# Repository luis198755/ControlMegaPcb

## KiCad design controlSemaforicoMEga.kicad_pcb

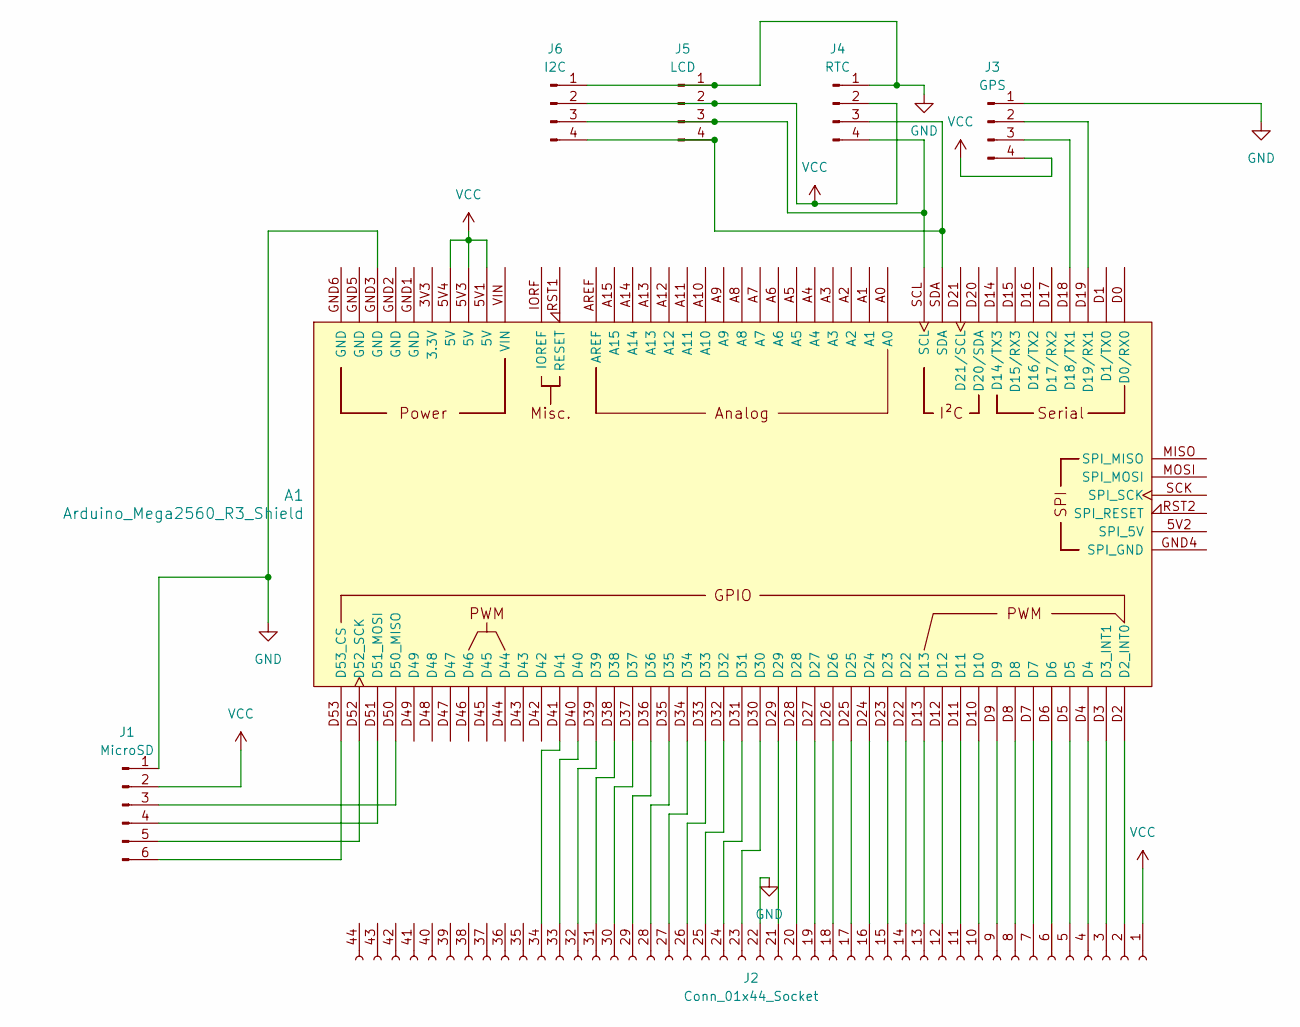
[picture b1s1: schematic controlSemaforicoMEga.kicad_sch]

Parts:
A1: Arduino_Mega2560_R3_Shield
J1: MicroSD; PinHeader_1x06_P2.54mm_Vertical
J2: Conn_01x44_Socket; con22sem
J3: GPS; PinHeader_1x04_P2.54mm_Vertical
J4: RTC; PinHeader_1x04_P2.54mm_Vertical
J5: LCD; PinHeader_1x04_P2.54mm_Vertical
J6: I2C; PinHeader_1x04_P2.54mm_Vertical

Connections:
GND: A1.GND3 (GND), J1.1, J2.22, J3.1, J4.1, J5.1, J6.1
unnamed: A1.D2 (D2_INT0), J2.2
unnamed: A1.D3 (D3_INT1), J2.3
unnamed: A1.D18 (D18/TX1), J3.3
unnamed: A1.D19 (D19/RX1), J3.2
unnamed: A1.D50 (D50_MISO), J1.3
unnamed: A1.D51 (D51_MOSI), J1.4
unnamed: A1.D52 (D52_SCK), J1.5
unnamed: A1.D53 (D53_CS), J1.6
unnamed: A1.D4, J2.4
unnamed: A1.D5, J2.5
unnamed: A1.D6, J2.6
unnamed: A1.D7, J2.7
unnamed: A1.D8, J2.8
unnamed: A1.D9, J2.9
unnamed: A1.D10, J2.10
unnamed: A1.D11, J2.11
unnamed: A1.D12, J2.12
unnamed: A1.D13, J2.13
unnamed: A1.D22, J2.14
unnamed: A1.D23, J2.15
unnamed: A1.D24, J2.16
unnamed: A1.D25, J2.17
unnamed: A1.D26, J2.18
unnamed: A1.D27, J2.19
unnamed: A1.D28, J2.20
unnamed: A1.D29, J2.21
unnamed: A1.D30, J2.23
unnamed: A1.D31, J2.24
unnamed: A1.D32, J2.25
unnamed: A1.D33, J2.26
unnamed: A1.D34, J2.27
unnamed: A1.D35, J2.28
unnamed: A1.D36, J2.29
unnamed: A1.D37, J2.30
unnamed: A1.D38, J2.31
unnamed: A1.D39, J2.32
unnamed: A1.D40, J2.33
unnamed: A1.D41, J2.34
unnamed: A1.SDA, J4.3, J5.4, J6.4
unnamed: A1.SCL, J4.4, J5.3, J6.3
VCC: A1.5V1 (5V), A1.5V3 (5V), A1.5V4 (5V), J1.2, J2.1, J3.4, J4.2, J5.2, J6.2

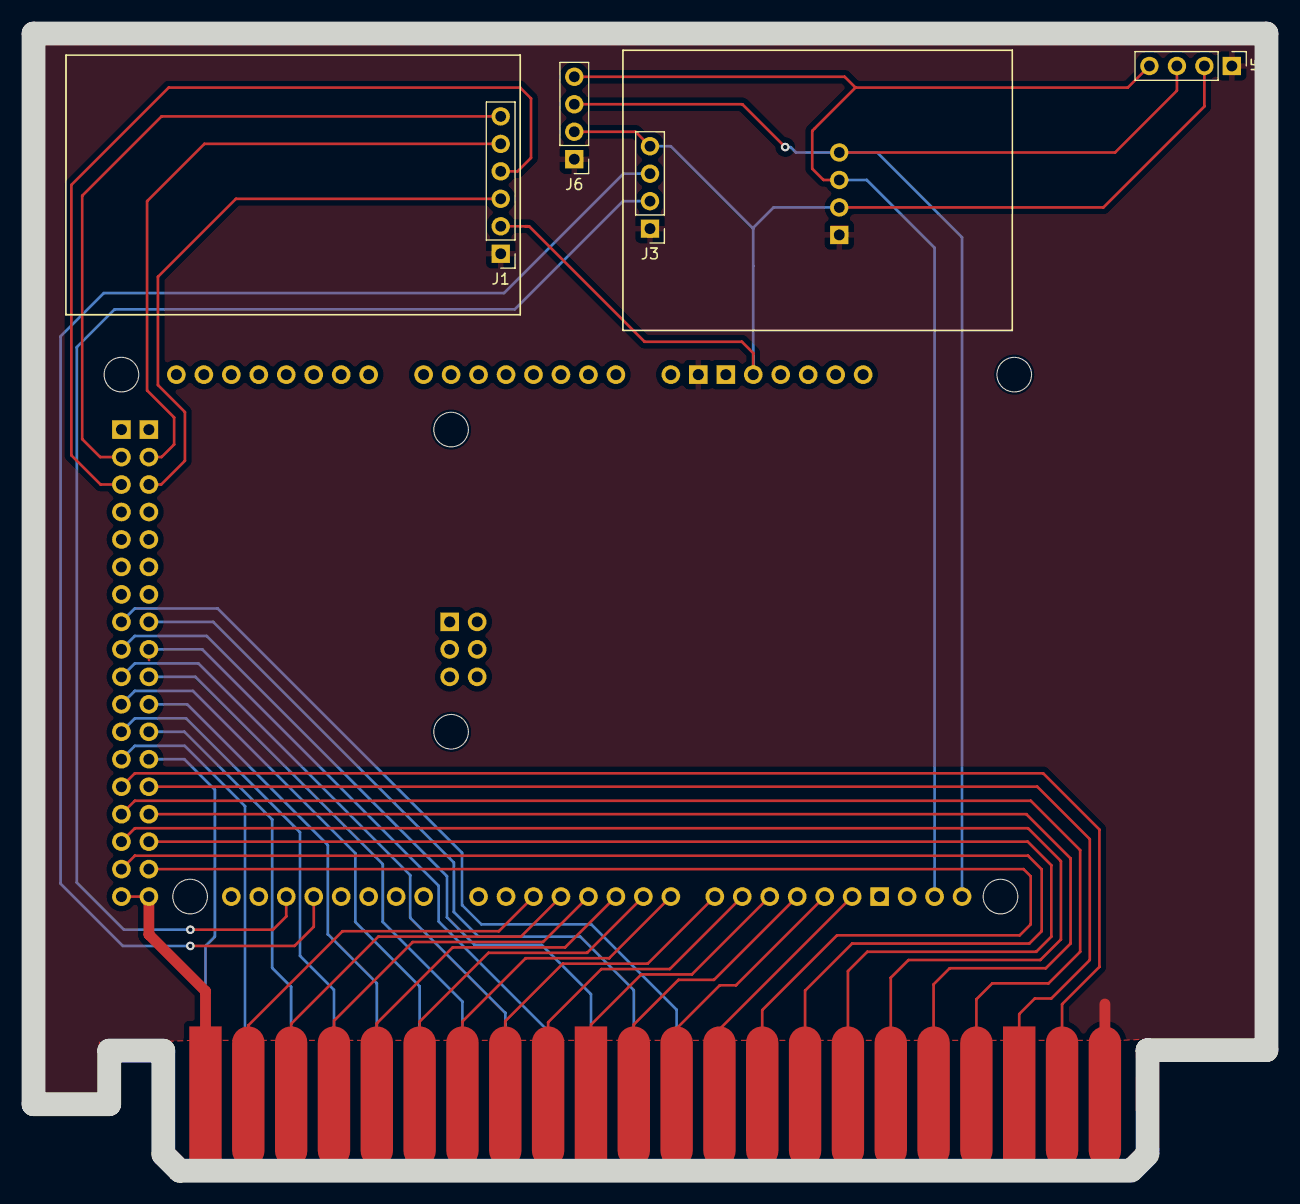
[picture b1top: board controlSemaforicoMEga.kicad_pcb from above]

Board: 2 copper layers, 114.0 x 105.1 mm, 7 parts (1 on the bottom side), 42 nets.

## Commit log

2024-05-22 add title
2024-05-22 10F
    Rack 10 Fases
